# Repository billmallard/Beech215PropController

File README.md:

# Beechcraft Bonanza Electric Prop — Digital Governor Controller
### Open-Source Replacement for the Airborne Electronics 350A

> **A modern, proportional-control replacement for the Airborne Electronics 350A solid-state propeller governor — for Beechcraft Bonanza models with the Beech 215-210 electric prop.**

> **Status, 2026-11-15:** hardware Rev 3.4 and firmware v3.1 are design-complete and unit-tested. **No Rev 3.4 board has been built, bench-tested or flown.** Earlier board revisions have known faults and must not be built. See [hardware_rev3_4/REV3_4_CHANGES.md](hardware_rev3_4/REV3_4_CHANGES.md).

---

## The Problem This Solves

The original Airborne Electronics 350A (covered under STC SA2700WE) uses a **bang-bang control architecture** — the prop motor runs at full voltage until the RPM crosses the target, then reverses. This causes constant RPM hunting, which is made worse by:

- Freshly overhauled prop motors with more torque than the 50-year-old electronics expected
- Aging capacitors and resistors in the original controller that shrink the deadband
- Rough magneto signal from high-time mags degrading the RPM sensing

**This project replaces only the electronics inside the governor box.** The 7-pin Cannon connector, airframe wiring, panel RPM knob, prop motor, limit switches, and relays are all unchanged. From the aircraft's perspective, the interface is identical to the original.

## What It Does Differently

| Feature | Original 350A | This Controller |
|---|---|---|
| Control type | Bang-bang (full voltage on/off) | Proportional — slows motor near setpoint |
| Deadband | Fixed by aging analog components | Software-configurable (default ±25 RPM) |
| Panel control | 10kΩ knob on connector pins E and F | The same knob on the same two wires. Nothing is added to the panel |
| RPM readout | None | None in the aircraft. An optional display can be plugged into the board on the bench |
| Setpoint transition | Follows the knob directly | Walks to the new knob setting at 100 RPM/sec — smooth, no lurch |
| Fail-safe | RPM signal loss → no action | Same: no magneto signal for 2 seconds → both relays off; governing resumes when the signal returns |
| Watchdog | None | Hardware watchdog resets MCU in 250ms if firmware stalls |
| Motor travel limits | Limit switches | Same: the aircraft's limit switches. The governor holds its output until the RPM is reached, as the original does |
| Failed output transistor | The relay stays energised and the prop runs to that pitch stop | The governor reads its own outputs back. An output that is live without being commanded opens a second switch ahead of both relay drivers within about 0.4 s, and the prop stops where it is. It stays off until the prop switch is cycled |

## Who This Is For

Any Beechcraft Bonanza (straight 35 through G35, A35–G35) equipped with:
- The Beech 215-210 electric prop
- An existing Airborne Electronics 350A installation (STC SA2700WE)

If you have the stock mechanical governor, this is not applicable.

---

## Regulatory Note

This project is designed for **owner-produced parts** under 14 CFR Part 21.303. The STC SA2700WE defines the system by its external interface — the 7-pin connector, wire assignments, and functional behavior — all of which are preserved exactly. The electronics inside the governor housing are replaced. **This is a major alteration and requires FAA Form 337 approval signed by an IA.** See [docs/REGULATORY.md](docs/REGULATORY.md) for a detailed discussion and suggested 337 language.

---

## Hardware Overview

The system is one unit: the governor box. The panel knob and all aircraft wiring stay as they are.

**Governor Box** (replaces the 350A housing, mounts in the same location):
- Arduino Nano (ATmega328P)
- 6N137 optocoupler on the magneto P-lead input
- 2N2222A + 2N2907A high-side relay drivers (NPN level shifter + PNP switch per channel)
- 1N4001 flyback diodes across each relay coil circuit
- Panel-control input for the original 10kΩ knob (connector pins E and F), with open-wire detection
- 12V input protection: resettable fuse and transient clamp
- LM2596S-5V DC-DC switching regulator
- Optional 4-pin header for an SSD1306 display, for bench work only

Current hardware revision: **3.4** (2026-11-15; boards are marked "REV 3.4" on the silkscreen). Rev 3.3 returned the panel control to the original potentiometer and fixed faults found in a design review of Rev 3.2; Rev 3.4 adds a series switch ahead of the relay drivers and unpopulated pads for an optional fault lamp. It needs firmware v3.1. **Rev 3, 3.1 and 3.2 boards must not be built or flown**; the reasons are in [hardware_rev3_3/REV3_3_CHANGES.md](hardware_rev3_3/REV3_3_CHANGES.md). Rev 3.3 was never made.

The PCB is a 100mm × 80mm 2-layer FR4 board, designed for JLCPCB fabrication at approximately **$2 for 5 boards**.

---

## Repository Structure

```
Beech215PropController/
├── README.md                        ← You are here
├── docs/
│   ├── ASSEMBLY.md                  ← Step-by-step build instructions
│   ├── BENCH_TEST.md                ← Ground test procedure before aircraft installation
│   ├── WIRING.md                    ← Connector pinout and wiring reference
│   ├── REGULATORY.md                ← FAA owner-produced parts guidance, 337 language
│   ├── TROUBLESHOOTING.md           ← Fault codes, common issues
│   ├── REWORK_FLYBACK_DIODES.md     ← Mandatory rework for Rev 3/3.1 boards
│   └── original_350A/               ← Scanned original Airborne Electronics documentation
├── firmware/
│   └── governor_350A/
│       ├── README.md                ← Flashing guide, serial console, unit tests
│       ├── governor_350A.ino        ← Arduino sketch (fully commented)
│       ├── platformio.ini           ← PlatformIO build config (AVR + native test)
│       └── test/                    ← Unity unit tests (runs on desktop, no hardware)
├── hardware_rev3_3/                 ← Rev 3.3: superseded by 3.4 before it was built. Its change record still applies
├── hardware_rev3_4/                 ← CURRENT hardware revision (designed, not yet built)
│   ├── REV3_4_CHANGES.md            ← What changed in 3.4 and why, verification evidence, open items
│   ├── board_top.png / board_bottom.png
│   ├── build_scripts/               ← Scripts that generated the 3.4 schematic, board and outputs
│   └── hardware/
│       ├── 350A_governor.kicad_sch  ← Schematic (KiCad 10)
│       ├── 350A_governor.kicad_pcb  ← PCB layout (KiCad 10)
│       ├── Schematic.pdf            ← Printable schematic
│       ├── BOM.md                   ← Bill of materials with part numbers and sources
│       ├── JLCPCB_INSTRUCTIONS.md   ← PCB ordering steps
│       └── gerbers/
│           └── 350A_governor_JLCPCB.zip  ← Ready-to-upload Gerber package
├── hardware_rev3_2/                 ← Previous revision (rotary-switch panel). Reference only; do not build
└── hardware_archive/                ← Superseded revisions (rev1, rev3, rev3_1, april2026)
```

---

## Quick Start

1. **Order the PCB** — Upload `hardware_rev3_4/hardware/gerbers/350A_governor_JLCPCB.zip` to [jlcpcb.com](https://jlcpcb.com). Default settings (2-layer, FR4, 1.6mm, HASL, green) are fine.
2. **Order components** — See [hardware_rev3_4/hardware/BOM.md](hardware_rev3_4/hardware/BOM.md). Total ~$50–90 for a complete build.
3. **Assemble** — Follow [docs/ASSEMBLY.md](docs/ASSEMBLY.md). All through-hole components; no SMD soldering.
4. **Flash firmware** — See [firmware/governor_350A/README.md](firmware/governor_350A/README.md) for full instructions (Arduino IDE, PlatformIO, and CLI). Set `PULSES_PER_REV`, `POT_RPM_MAX` and `POT_RPM_MIN` for your engine before flashing.
5. **Bench test** — Build the test harness described in [docs/BENCH_TEST.md](docs/BENCH_TEST.md) and verify operation before touching the aircraft.
6. **Install** — Follow [docs/ASSEMBLY.md](docs/ASSEMBLY.md) aircraft installation section. Have your IA present.

---

## Engine Compatibility

Set `PULSES_PER_REV` in the firmware before flashing:

| Engine | Cylinders | PULSES_PER_REV |
|---|---|---|
| Continental IO-470 | 6 | 3 |
| Continental IO-520 | 6 | 3 |
| Continental E-185/E-225 | 6 | 3 |
| Lycoming O-435 | 6 | 3 |

All early Bonanzas use Continental 6-cylinder engines. `PULSES_PER_REV = 3` is correct for all of them.

---

## Contributing

This project is maintained by the Bonanza owner community. Pull requests welcome for:
- Firmware improvements (better control algorithms, additional safety checks)
- Documentation corrections
- Hardware revisions (alternative component footprints)
- Flight test data and tuning recommendations

Please open an issue before starting significant work so efforts aren't duplicated.

---

## Security

This repository uses layered secret-prevention controls. See [SECURITY.md](SECURITY.md) for the full policy including vulnerability reporting and incident response steps.

| Layer | Tool | Trigger |
|---|---|---|
| Local pre-commit | `tools/security/scan_secrets.py` | Every `git commit` (staged files) |
| CI — SAST | CodeQL (C/C++ + Python) | Push, PR, weekly |
| CI — Secret scan | Gitleaks | Push, PR, weekly (full history) |

**Quick setup after cloning:**
```
pip install pre-commit
pre-commit install
```

Recommended GitHub repository settings: enable **Secret scanning**, **Push protection**, and **Dependabot** (Settings → Security).

---

## License

MIT License. See LICENSE file. This hardware and firmware may be freely built, modified, and used for personal aircraft. Commercial reproduction or sale requires separate arrangement.

---

## Acknowledgments

Richard Keiter of Airborne Electronics, Healdsburg CA, designed the original 350A and made it repairable by owners. This project is built on his philosophy. The complete original documentation is preserved in [docs/original_350A/](docs/original_350A/) for reference.

---

*This project is not affiliated with Beechcraft, Textron Aviation, or Airborne Electronics. It is an independent owner-community project. Install only with appropriate FAA authorization.*

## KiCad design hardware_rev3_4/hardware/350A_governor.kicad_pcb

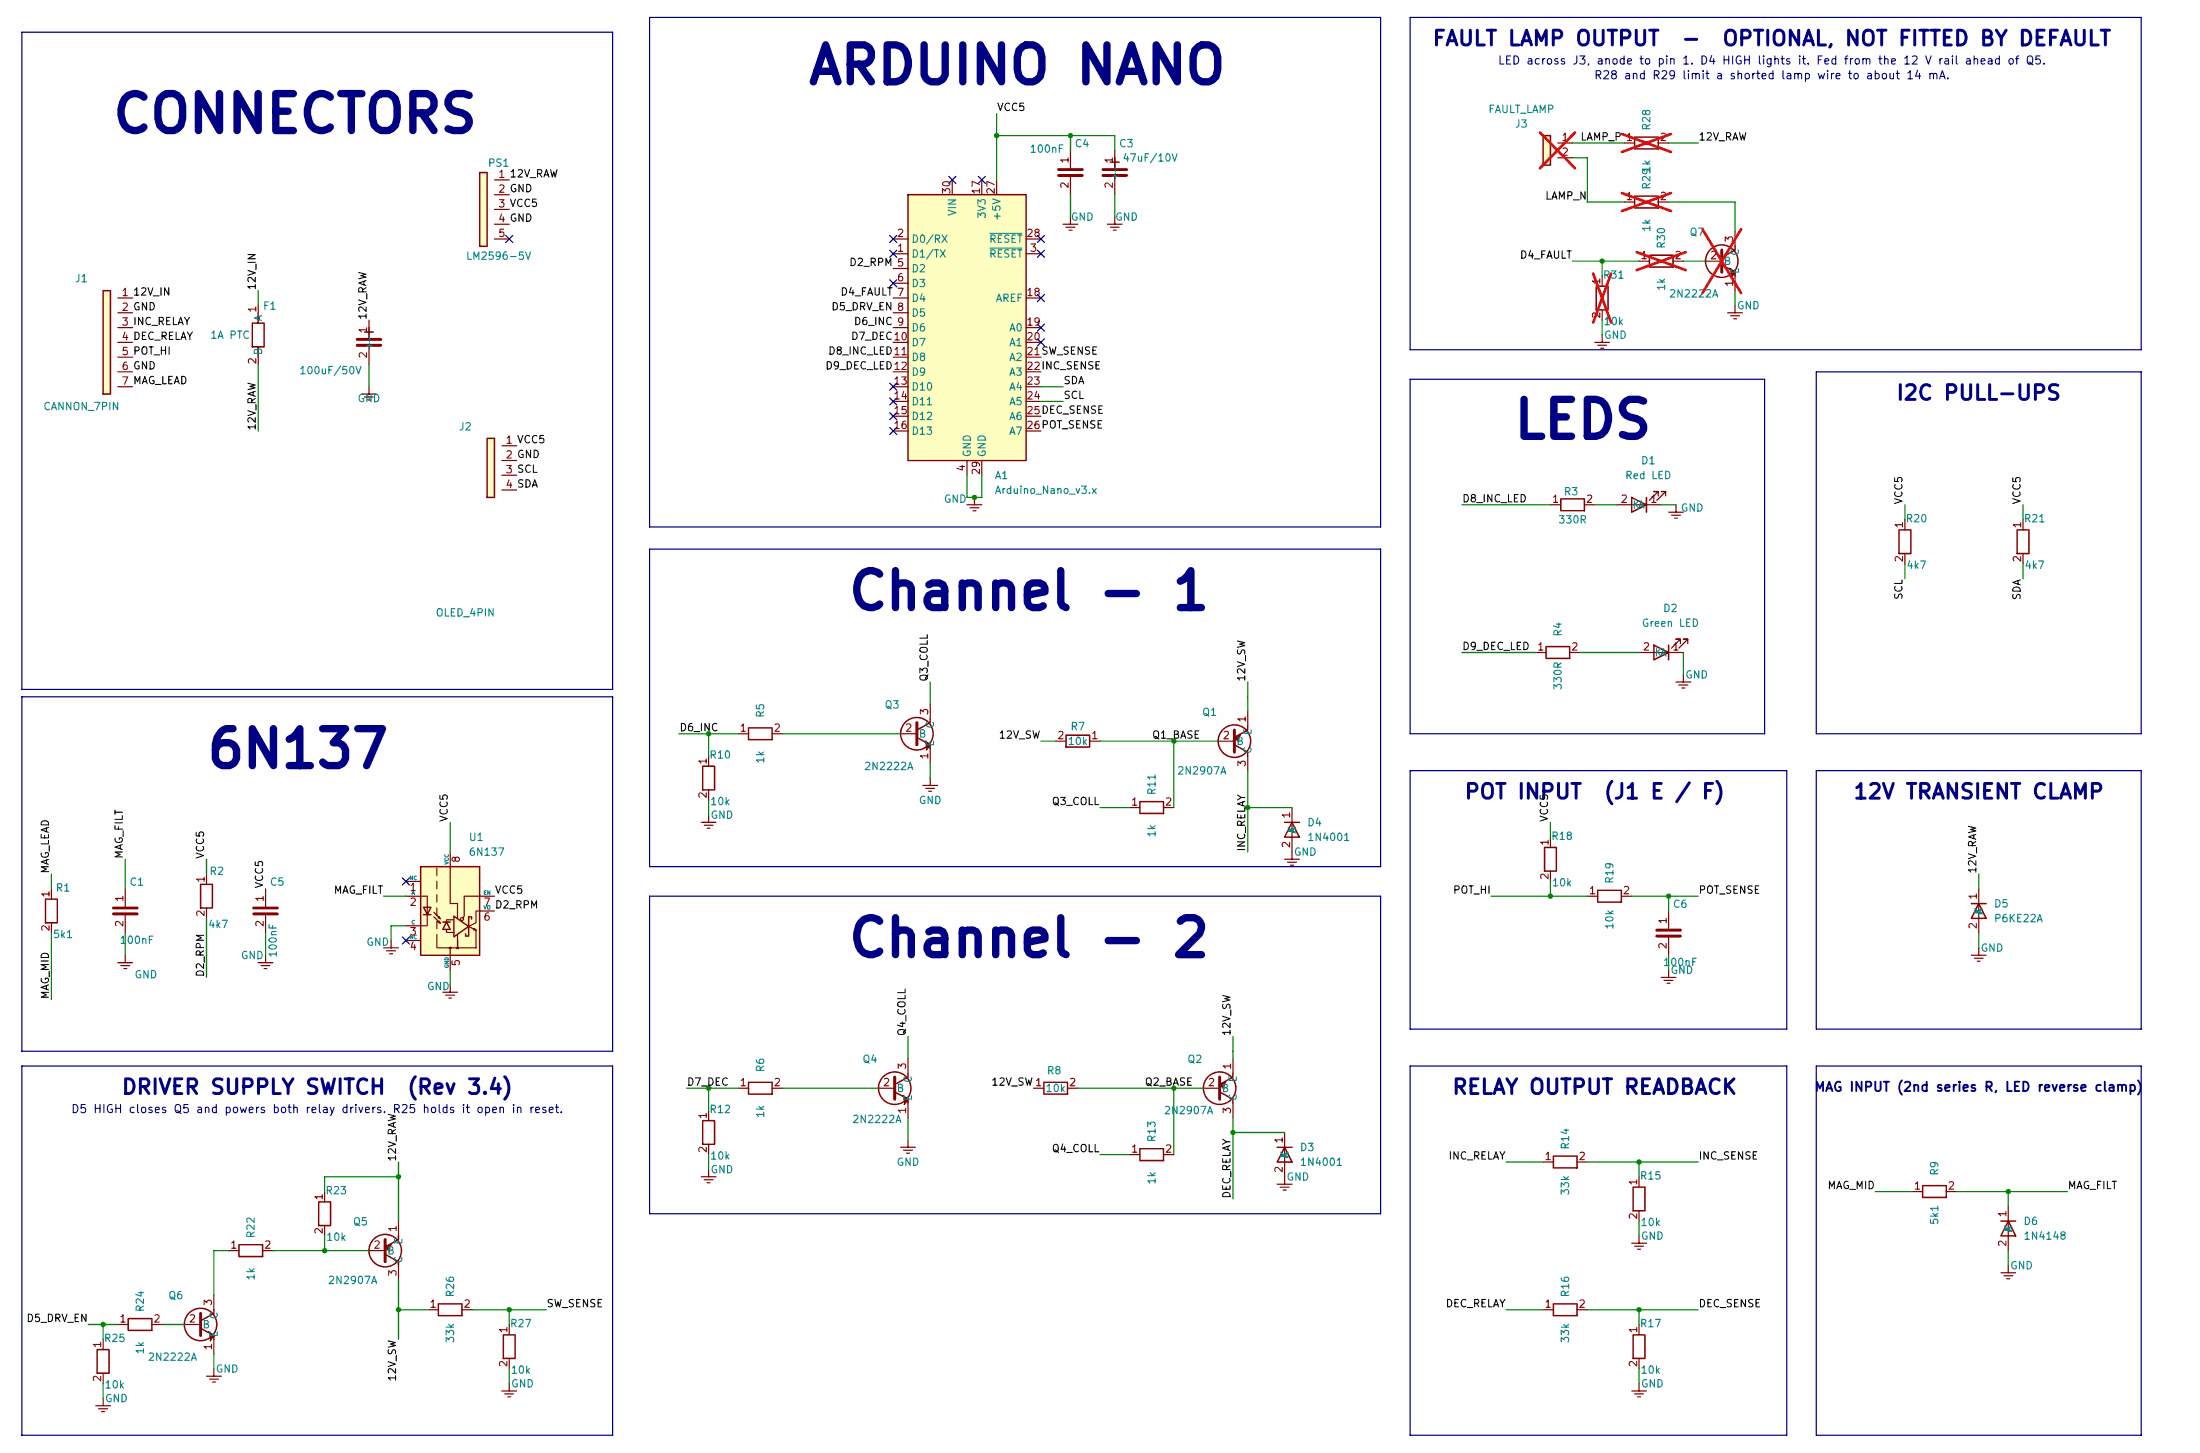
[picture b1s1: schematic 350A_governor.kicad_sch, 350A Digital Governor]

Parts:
A1: Arduino_Nano_v3.x; Arduino_Nano
C1, C4, C5, C6: 100nF; C_Disc_D3.8mm_W2.6mm_P2.50mm
C2: 100uF/50V; CP_Radial_D8.0mm_P3.50mm
C3: 47uF/10V; CP_Radial_D8.0mm_P3.80mm
D1: Red LED; LED_D3.0mm
D2: Green LED; LED_D3.0mm
D3, D4: 1N4001; D_DO-41_SOD81_P10.16mm_Horizontal
D5: P6KE22A; D_DO-15_P10.16mm_Horizontal
D6: 1N4148; D_DO-35_SOD27_P7.62mm_Horizontal
F1: 1A PTC; Fuse_BelFuse_0ZRE0100FF_L18.7mm_W5.1mm
J1: CANNON_7PIN; PinHeader_1x07_P2.54mm_Vertical_Pin7Offset
J2: OLED_4PIN; PinHeader_1x04_P2.54mm_Vertical
J3: FAULT_LAMP; PinHeader_1x02_P2.54mm_Vertical; not fitted
PS1: LM2596-5V; PinHeader_1x05_P2.54mm_Vertical
Q1, Q2, Q5: 2N2907A; TO-92L_Inline_Wide
Q3, Q4, Q6: 2N2222A; TO92254P470H750-3
Q7: 2N2222A; TO92254P470H750-3; not fitted
R1, R9: 5k1; R_Axial_DIN0207_L6.3mm_D2.5mm_P7.62mm_Horizontal
R2: 4k7; R_Axial_DIN0207_L6.3mm_D2.5mm_P15.24mm_Horizontal
R3, R4: 330R; R_Axial_DIN0207_L6.3mm_D2.5mm_P7.62mm_Horizontal
R5, R6, R11, R13, R22, R24: 1k; R_Axial_DIN0207_L6.3mm_D2.5mm_P7.62mm_Horizontal
R7, R8, R10, R12, R15, R17, R18, R19, R23, R25, R27: 10k; R_Axial_DIN0207_L6.3mm_D2.5mm_P7.62mm_Horizontal
R14, R16, R26: 33k; R_Axial_DIN0207_L6.3mm_D2.5mm_P7.62mm_Horizontal
R20, R21: 4k7; R_Axial_DIN0207_L6.3mm_D2.5mm_P7.62mm_Horizontal
R28: 1k; R_Axial_DIN0207_L6.3mm_D2.5mm_P15.24mm_Horizontal; not fitted
R29, R30: 1k; R_Axial_DIN0207_L6.3mm_D2.5mm_P7.62mm_Horizontal; not fitted
R31: 10k; R_Axial_DIN0207_L6.3mm_D2.5mm_P7.62mm_Horizontal; not fitted
U1: 6N137; DIP-8_W7.62mm

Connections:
/12V_IN: F1.1 (A), J1.1
/12V_RAW: C2.1 (+), D5.1 (K), F1.2 (B), PS1.1, Q5.1 (E), R23.1, R28.2
/12V_SW: Q1.1 (E), Q2.1 (E), Q5.3 (C), R7.2, R8.1, R26.1
/D2_RPM: A1.5 (D2), R2.2, U1.6 (VO)
/D4_FAULT: A1.7 (D4), R30.1, R31.1
/D5_DRV_EN: A1.8 (D5), R24.1, R25.1
/D6_INC: A1.9 (D6), R5.1, R10.1
/D7_DEC: A1.10 (D7), R6.1, R12.1
/D8_INC_LED: A1.11 (D8), R3.1
/D9_DEC_LED: A1.12 (D9), R4.1
/DEC_RELAY: D3.1 (K), J1.4, Q2.3 (C), R16.1
/DEC_SENSE: A1.25 (A6), R16.2, R17.1
/INC_RELAY: D4.1 (K), J1.3, Q1.3 (C), R14.1
/INC_SENSE: A1.22 (A3), R14.2, R15.1
/LAMP_N: J3.2, R29.1
/LAMP_P: J3.1, R28.1
/MAG_FILT: C1.1, D6.1 (K), R9.2, U1.2 (A)
/MAG_LEAD: J1.7, R1.1
/MAG_MID: R1.2, R9.1
/POT_HI: J1.5, R18.2, R19.1
/POT_SENSE: A1.26 (A7), C6.1, R19.2
/Q1_BASE: Q1.2 (B), R7.1, R11.2
/Q2_BASE: Q2.2 (B), R8.2, R13.2
/Q3_COLL: Q3.3 (C), R11.1
/Q4_COLL: Q4.3 (C), R13.1
/SCL: A1.24 (A5), J2.3, R20.2
/SDA: A1.23 (A4), J2.4, R21.2
/SW_SENSE: A1.21 (A2), R26.2, R27.1
/VCC5: A1.27 (+5V), C3.1 (+), C4.1, C5.1, J2.1, PS1.3, R2.1, R18.1, R20.1, R21.1, U1.7 (EN), U1.8 (VCC)
GND: A1.4 (GND), A1.29 (GND), C1.2, C2.2 (-), C3.2 (-), C4.2, C5.2, C6.2, D1.1 (K), D2.1 (K), D3.2 (A), D4.2 (A), D5.2 (A), D6.2 (A), J1.2, J1.6, J2.2, PS1.2, PS1.4, Q3.1 (E), Q4.1 (E), Q6.1 (E), Q7.1 (E), R10.2, R12.2, R15.2, R17.2, R25.2, R27.2, R31.2, U1.3 (C), U1.5 (GND)
unnamed: D1.2 (A), R3.2
unnamed: D2.2 (A), R4.2
unnamed: Q3.2 (B), R5.2
unnamed: Q4.2 (B), R6.2
unnamed: Q5.2 (B), R22.2, R23.2
unnamed: Q6.2 (B), R24.2
unnamed: Q6.3 (C), R22.1
unnamed: Q7.2 (B), R30.2
unnamed: Q7.3 (C), R29.2

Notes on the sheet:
ARDUINO NANO
Channel - 1
CONNECTORS
6N137
Channel - 2
LEDS
POT INPUT (J1 E / F)
RELAY OUTPUT READBACK
I2C PULL-UPS
12V TRANSIENT CLAMP
MAG INPUT (2nd series R, LED reverse clamp)
DRIVER SUPPLY SWITCH (Rev 3.4)
D5 HIGH closes Q5 and powers both relay drivers. R25 holds it open in reset.
FAULT LAMP OUTPUT - OPTIONAL, NOT FITTED BY DEFAULT
LED across J3, anode to pin 1. D4 HIGH lights it. Fed from the 12 V rail ahead of Q5.
R28 and R29 limit a shorted lamp wire to about 14 mA.

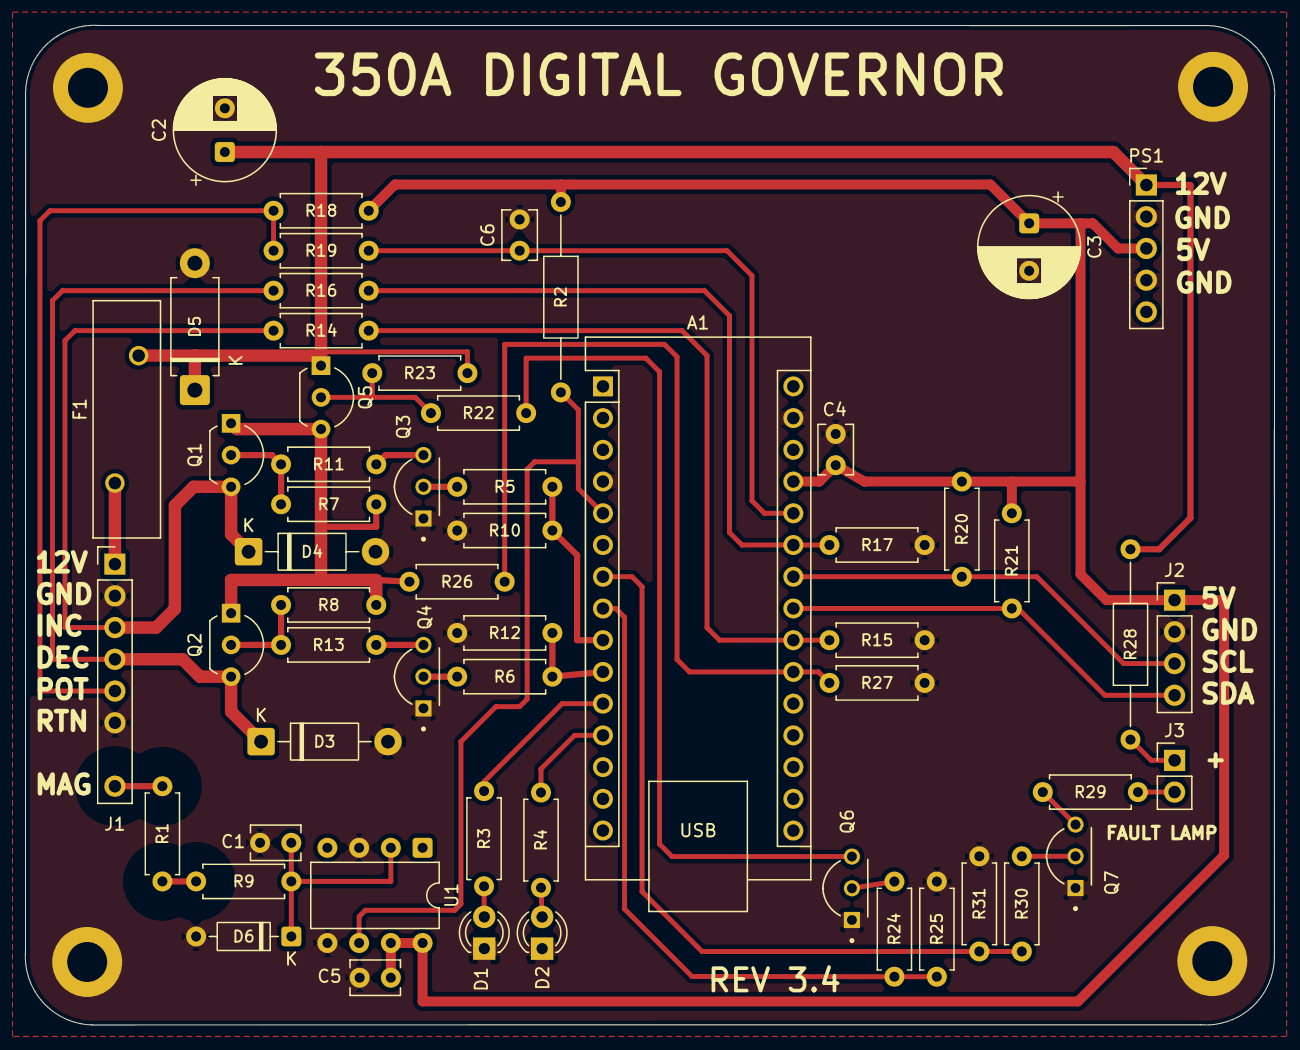
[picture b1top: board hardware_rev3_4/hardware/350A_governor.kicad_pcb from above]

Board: 2 copper layers, 100.0 x 80.0 mm, 57 parts (0 on the bottom side), 39 nets.

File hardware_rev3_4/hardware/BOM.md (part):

# Bill of Materials — Rev 3.4

Complete parts list for one governor build. All parts available from Digi-Key, Mouser, or Amazon.
Links are to Digi-Key where possible — they're reliable, stock everything, and ship fast.

**Estimated total cost: $50–90** depending on sourcing (Amazon vs. Digi-Key, bulk vs. singles)

Rev 3.4 reads the original 350A panel control (10k, connector pins E and F), so there is no panel unit to buy or build. What changed from Rev 3.3 and why: [../REV3_4_CHANGES.md](../REV3_4_CHANGES.md). Rev 3.4 adds the driver supply switch (Q5, Q6, R22–R27), which is fitted on every board, and an optional fault-lamp output (J3, Q7, R28–R31), which is **not** fitted by default and has its own section below.

---

## PCB

| Item | Specification | Qty | Source | Est. Cost | Notes |
|---|---|---|---|---|---|
| Governor PCB | 100×80mm 2-layer FR4 | 5 | JLCPCB | ~$2 + shipping | Upload `gerbers/350A_governor_JLCPCB.zip`; default settings; you get 5, use 1 |

**JLCPCB order settings:**
- Base Material: FR4
- Layers: 2
- PCB Thickness: 1.6mm
- Surface Finish: HASL (with lead) — cheapest and fine for this application
- Copper Weight: 1oz
- Everything else: defaults

---

## ICs and Active Components

| Ref | Part | Description | Digi-Key PN | Qty | Est. Cost | Notes |
|---|---|---|---|---|---|---|
| A1 | Arduino Nano (ATmega328P) | Microcontroller | — | 1 | $4–8 | Buy the CH340 version (most common on Amazon/eBay). Avoid Nano Every — different pinout. |
| U1 | 6N137 | High-speed optocoupler | 516-2878-5-ND | 1 | $0.60 | DIP-8. Do not substitute 4N25/4N35 — too slow for mag pulses. |
| PS1 | LM2596S-5V Module | DC-DC 5V switching regulator | — | 1 | $1–3 | Pre-built module. **Must be labeled "5V" not adjustable.** Verify output before installing. Available on Amazon, 10-packs for $8. |
| OLED (optional) | SSD1306 1.3" OLED | I2C display 128×64 | — | 0–1 | $6–10 | **Optional bench/service display** on J2. Not needed in the aircraft; the governor runs without it. Must be I2C, 128×64, 4-pin. J2 order is 5V, GND, SCL, SDA: check the pin order of your module before plugging it in. |

---

## Transistors — High-Side Relay Driver

Two-channel NPN+PNP circuit replacing the ULN2003A from Rev 2, plus (from Rev 3.4) a third NPN+PNP pair in series with the supply to both channels. All TO-92 package. Q1/Q2/Q5 pads are on a 2.54 mm pitch: spread the outer two leads slightly to fit.

| Ref | Part | Type | Digi-Key PN | Qty | Est. Cost | Notes |
|---|---|---|---|---|---|---|
| Q1, Q2 | 2N2907A | PNP — high-side switch | 2N2907A-ND | 2 | ~$0.50 ea | TO-92L. Switches +12V to relay coil. |
| Q3, Q4 | 2N2222A | NPN — level shifter | 2N2222A-ND | 2 | ~$0.30 ea | TO-92. Driven by Nano 5V logic. |
| Q5 | 2N2907A | PNP — driver supply switch | 2N2907A-ND | 1 | ~$0.50 | TO-92L, same part as Q1/Q2. In series with the +12V feed to both relay drivers, so the firmware can cut the supply to a driver that has failed short. |
| Q6 | 2N2222A | NPN — level shifter for Q5 | 2N2222A-ND | 1 | ~$0.30 | TO-92, same part as Q3/Q4. Driven by Nano D5. |

---

## Passives — Resistors

All resistors: 1/4W metal film, 1% tolerance

| Ref | Value | Digi-Key PN | Qty | Notes |
|---|---|---|---|---|
| R1, R9 | 5.1kΩ | 5.1KEBK-ND | 2 | Magneto input series resistors (two in series share the voltage) |
| R2 | 4.7kΩ | 4.7KEBK-ND | 1 | Optocoupler pull-up. **Pads are 15.24 mm apart** — bend the leads wider than the others. |
| R3, R4 | 330Ω | 330EBK-ND | 2 | LED current limiters |
| R5, R6 | 1kΩ | 1.0KEBK-ND | 2 | NPN base resistors (Q3, Q4) |
| R7, R8 | 10kΩ | 10KEBK-ND | 2 | PNP base pull-up to +12V (Q1, Q2) |
| R10, R12 | 10kΩ | 10KEBK-ND | 2 | Driver input pull-downs: hold the relays off while the Nano is in reset |
| R11, R13 | 1kΩ | 1.0KEBK-ND | 2 | PNP base series resistors (Q1, Q2). Sized for relay coils up to about 250 mA — see REV3_3_CHANGES.md |
| R14, R16 | 33kΩ | 33KEBK-ND | 2 | Relay output readback dividers (top) |
| R15, R17 | 10kΩ | 10KEBK-ND | 2 | Relay output readback dividers (bottom) |
| R18 | 10kΩ | 10KEBK-ND | 1 | Pot pull-up to 5V. Sets the pot scale: use 1% |
| R19 | 10kΩ | 10KEBK-ND | 1 | Pot input series protection |
| R20, R21 | 4.7kΩ | 4.7KEBK-ND | 2 | I2C pull-ups (only matter if a display is fitted) |
| R22 | 1kΩ | 1.0KEBK-ND | 1 | Q5 base series resistor (same sizing as R11/R13) |
| R23 | 10kΩ | 10KEBK-ND | 1 | Q5 base pull-up to +12V: holds the switch open unless Q6 pulls it closed |
| R24 | 1kΩ | 1.0KEBK-ND | 1 | Q6 base resistor, from Nano D5 |
| R25 | 10kΩ | 10KEBK-ND | 1 | D5 pull-down: holds the switch open while the Nano is in reset |
| R26 | 33kΩ | 33KEBK-ND | 1 | Switched-rail readback divider (top), to Nano A2 |
| R27 | 10kΩ | 10KEBK-ND | 1 | Switched-rail readback divider (bottom). Also discharges the switched rail when Q5 is open |

**Tip:** 10kΩ ×11 (R7, R8, R10, R12, R15, R17, R18, R19, R23, R25, R27), 1kΩ ×6 (R5, R6, R11, R13, R22, R24), 4.7kΩ ×3, 5.1kΩ ×2, 33kΩ ×3, 330Ω ×2. The optional fault lamp adds 1kΩ ×3 and 10kΩ ×1.
The Digi-Key numbers for the new values follow the pattern of the existing lines; confirm each resolves before ordering.

---

## Passives — Capacitors

| Ref | Value | Type | Digi-Key PN | Qty | Notes |
|---|---|---|---|---|---|
| C1, C4, C5, C6 | 100nF (0.1µF) | Ceramic disc | 445-173-ND | 4 | Non-polarized; marked "104". C6 filters the pot input. |
| C2 | 100µF 50V | Electrolytic, 8 mm diameter, 3.5 mm lead pitch, 105°C | — | 1 | **POLARIZED** — observe polarity. 12V bulk cap, now behind the fuse. The 50V rating is deliberate; do not fit a 25V part. |
| C3 | 47µF 10V | Electrolytic | 493-1205-ND | 1 | **POLARIZED** — observe polarity. 5V output filter cap. |

---

## Protection — Diodes and Fuse

| Ref | Part | Digi-Key PN | Qty | Notes |
|---|---|---|---|---|
| D3, D4 | 1N4001 | 1N4001FSCT-ND | 2 | Flyback diodes across each relay coil circuit — clamp the coil's inductive spike when the PNP switches off. **Do not omit.** Polarity: cathode (band) to the relay output pad (marked "K" on silkscreen), anode to ground. |
| D5 | P6KE22A | — | 1 | 600 W unidirectional TVS, DO-15. Clamps 12V bus transients and, with F1, protects against reversed polarity. Band (cathode) to the "K" mark. Do not fit the bidirectional P6KE22CA. |
| D6 | 1N4148 | 1N4148FS-ND | 1 | Reverse clamp across the optocoupler LED. Band to the "K" mark. |
| F1 | 1A PTC resettable fuse | Bel Fuse 0ZRE0100FF | 1 | In series with the +12V input. **The footprint fits the 0ZRE0100FF: 10.2 mm lead spacing.** Smaller PTCs with 5.1 mm spacing do not fit. |

---

## Optional fault lamp (not fitted by default)

These six parts drive an external fault lamp from Nano D4. **Leave all of them off the board unless the lamp is wanted.** The pads, tracks and silkscreen are on every board; nothing else on the board depends on them, and they are marked do-not-populate in the schematic.

| Ref | Part | Digi-Key PN | Qty | Notes |
|---|---|---|---|---|
| J3 | 1×2 2.54mm male header | — | 0–1 | "FAULT LAMP". An LED wires directly across the two pins, anode to pin 1 (marked "+"). No external resistor is needed. |
| Q7 | 2N2222A | 2N2222A-ND | 0–1 | TO-92, same part and pinout as Q3/Q4/Q6. Switches the lamp return. |
| R28 | 1kΩ | 1.0KEBK-ND | 0–1 | From the +12V rail (ahead of Q5, so the lamp works with the driver supply switched off) to J3 pin 1. **Pads are 15.24 mm apart** — bend the leads wider, as for R2. |
| R29 | 1kΩ | 1.0KEBK-ND | 0–1 | From J3 pin 2 to Q7. With R28 it limits a lamp wire shorted to ground or to the bus to about 14 mA. |
| R30 | 1kΩ | 1.0KEBK-ND | 0–1 | Q7 base resistor, from Nano D4 |
| R31 | 10kΩ | 10KEBK-ND | 0–1 | D4 pull-down: lamp off while the Nano is in reset |

Lamp current is about 5 mA with a red or green LED on a 14 V bus.

---

## Indicators

| Ref | Part | Digi-Key PN | Qty | Notes |
|---|---|---|---|---|
| D1 | 3mm Red LED | 754-1264-ND | 1 | Standard brightness; INC indicator |
| D2 | 3mm Green LED | 754-1221-ND | 1 | Standard brightness; DEC indicator |
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
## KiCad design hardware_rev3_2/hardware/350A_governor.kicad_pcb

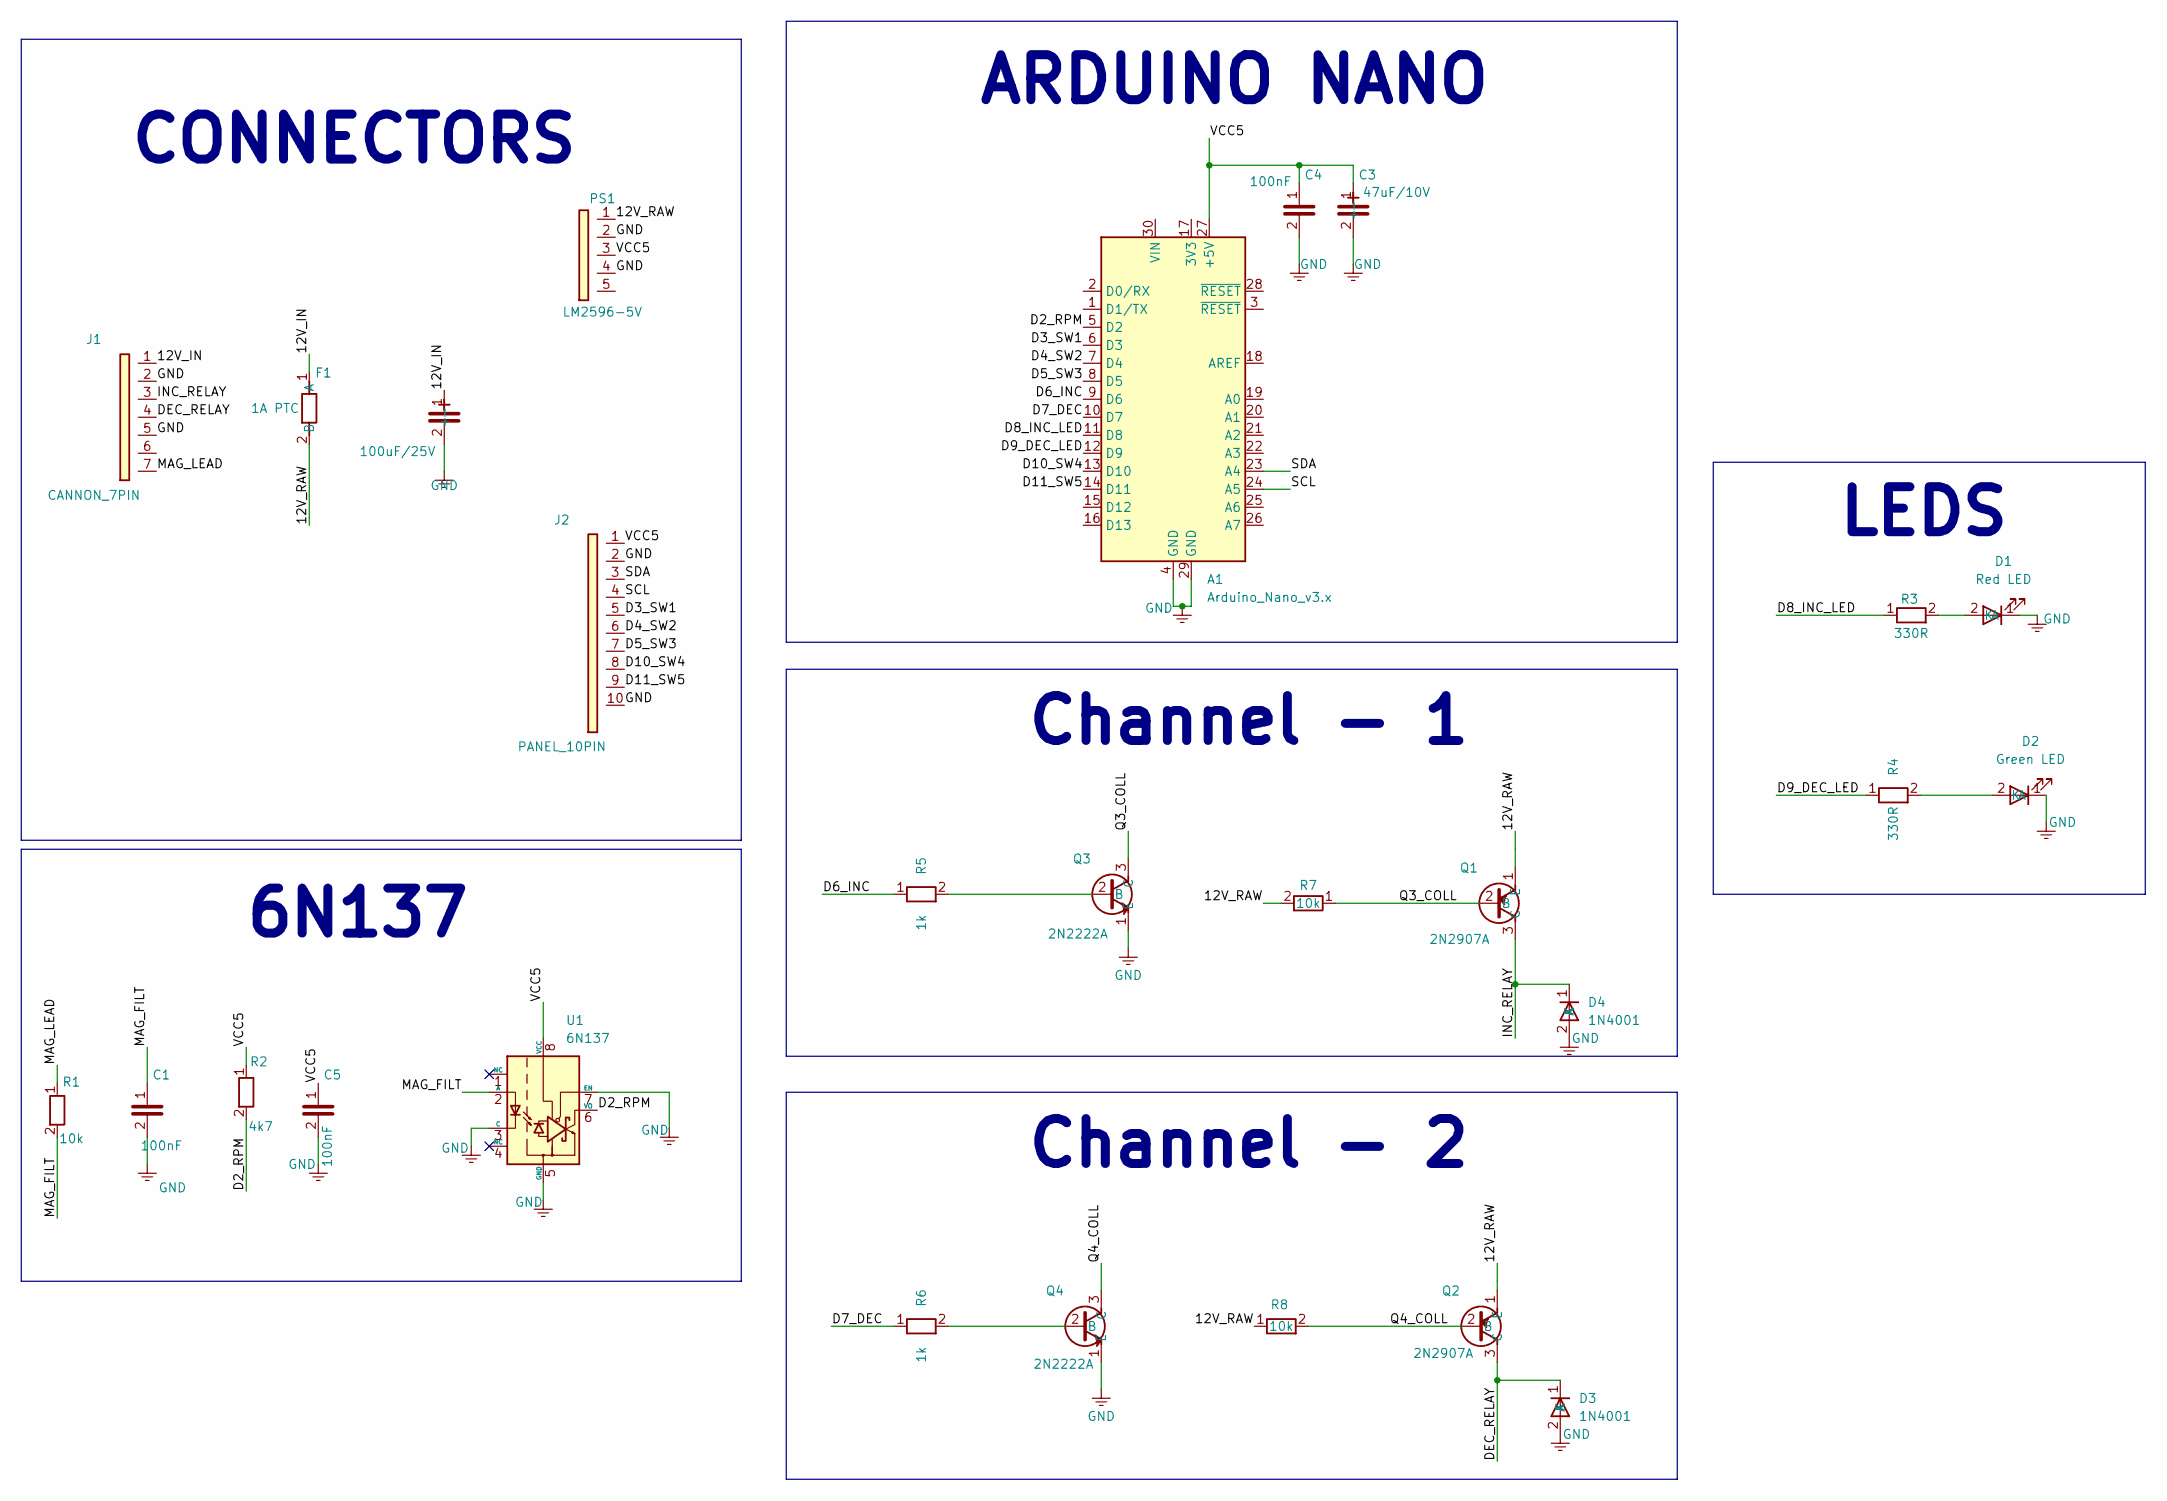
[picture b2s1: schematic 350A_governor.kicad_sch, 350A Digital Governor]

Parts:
A1: Arduino_Nano_v3.x; Arduino_Nano
C1, C4, C5: 100nF; C_Disc_D3.8mm_W2.6mm_P2.50mm
C2: 100uF/25V; CP_Radial_D5.0mm_P2.50mm
C3: 47uF/10V; CP_Radial_D8.0mm_P3.80mm
D1: Red LED
D2: Green LED
D3, D4: 1N4001; D_DO-41_SOD81_P10.16mm_Horizontal
F1: 1A PTC; Fuse_BelFuse_0ZRE0012FF_L8.3mm_W3.8mm
J1: CANNON_7PIN; PinHeader_1x07_P2.54mm_Vertical
J2: PANEL_10PIN; PinHeader_1x10_P2.54mm_Vertical
PS1: LM2596-5V; PinHeader_1x05_P2.54mm_Vertical
Q1, Q2: 2N2907A; TO-92L_Inline
Q3, Q4: 2N2222A; TO92254P470H750-3
R1, R7, R8: 10k; R_Axial_DIN0207_L6.3mm_D2.5mm_P7.62mm_Horizontal
R2: 4k7; R_Axial_DIN0207_L6.3mm_D2.5mm_P7.62mm_Horizontal
R3, R4: 330R; R_Axial_DIN0207_L6.3mm_D2.5mm_P7.62mm_Horizontal
R5, R6: 1k; R_Axial_DIN0207_L6.3mm_D2.5mm_P7.62mm_Horizontal
U1: 6N137; DIP-8_W7.62mm

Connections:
/12V_IN: C2.1 (+), F1.1 (A), J1.1
/12V_RAW: F1.2 (B), PS1.1, Q1.1 (E), Q2.1 (E), R7.2, R8.1
/D2_RPM: A1.5 (D2), R2.2, U1.6 (VO)
/D3_SW1: A1.6 (D3), J2.5
/D4_SW2: A1.7 (D4), J2.6
/D5_SW3: A1.8 (D5), J2.7
/D6_INC: A1.9 (D6), R5.1
/D7_DEC: A1.10 (D7), R6.1
/D8_INC_LED: A1.11 (D8), R3.1
/D9_DEC_LED: A1.12 (D9), R4.1
/D10_SW4: A1.13 (D10), J2.8
/D11_SW5: A1.14 (D11), J2.9
/DEC_RELAY: D3.1 (K), J1.4, Q2.3 (C)
/INC_RELAY: D4.1 (K), J1.3, Q1.3 (C)
/MAG_FILT: C1.1, R1.2, U1.2 (A)
/MAG_LEAD: J1.7, R1.1
/Q3_COLL: Q1.2 (B), Q3.3 (C), R7.1
/Q4_COLL: Q2.2 (B), Q4.3 (C), R8.2
/SCL: A1.24 (A5), J2.4
/SDA: A1.23 (A4), J2.3
/VCC5: A1.27 (+5V), C3.1 (+), C4.1, C5.1, J2.1, PS1.3, R2.1, U1.8 (VCC)
GND: A1.4 (GND), A1.29 (GND), C1.2, C2.2 (-), C3.2 (-), C4.2, C5.2, D1.1 (K), D2.1 (K), D3.2 (A), D4.2 (A), J1.2, J1.5, J2.2, J2.10, PS1.2, PS1.4, Q3.1 (E), Q4.1 (E), U1.3 (C), U1.5 (GND), U1.7 (EN)
unnamed: D1.2 (A), R3.2
unnamed: D2.2 (A), R4.2
unnamed: Q3.2 (B), R5.2
unnamed: Q4.2 (B), R6.2

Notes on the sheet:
ARDUINO NANO
Channel - 1
CONNECTORS
6N137
Channel - 2
LEDS

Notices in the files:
firmware/governor_350A/governor_350A.ino:
MIT License — see repository LICENSE file
